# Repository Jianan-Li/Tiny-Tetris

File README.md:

# Tiny-Tetris

Click <a href="http://www.jianan.li/tiny-tetris">here</a> for more info on this project.

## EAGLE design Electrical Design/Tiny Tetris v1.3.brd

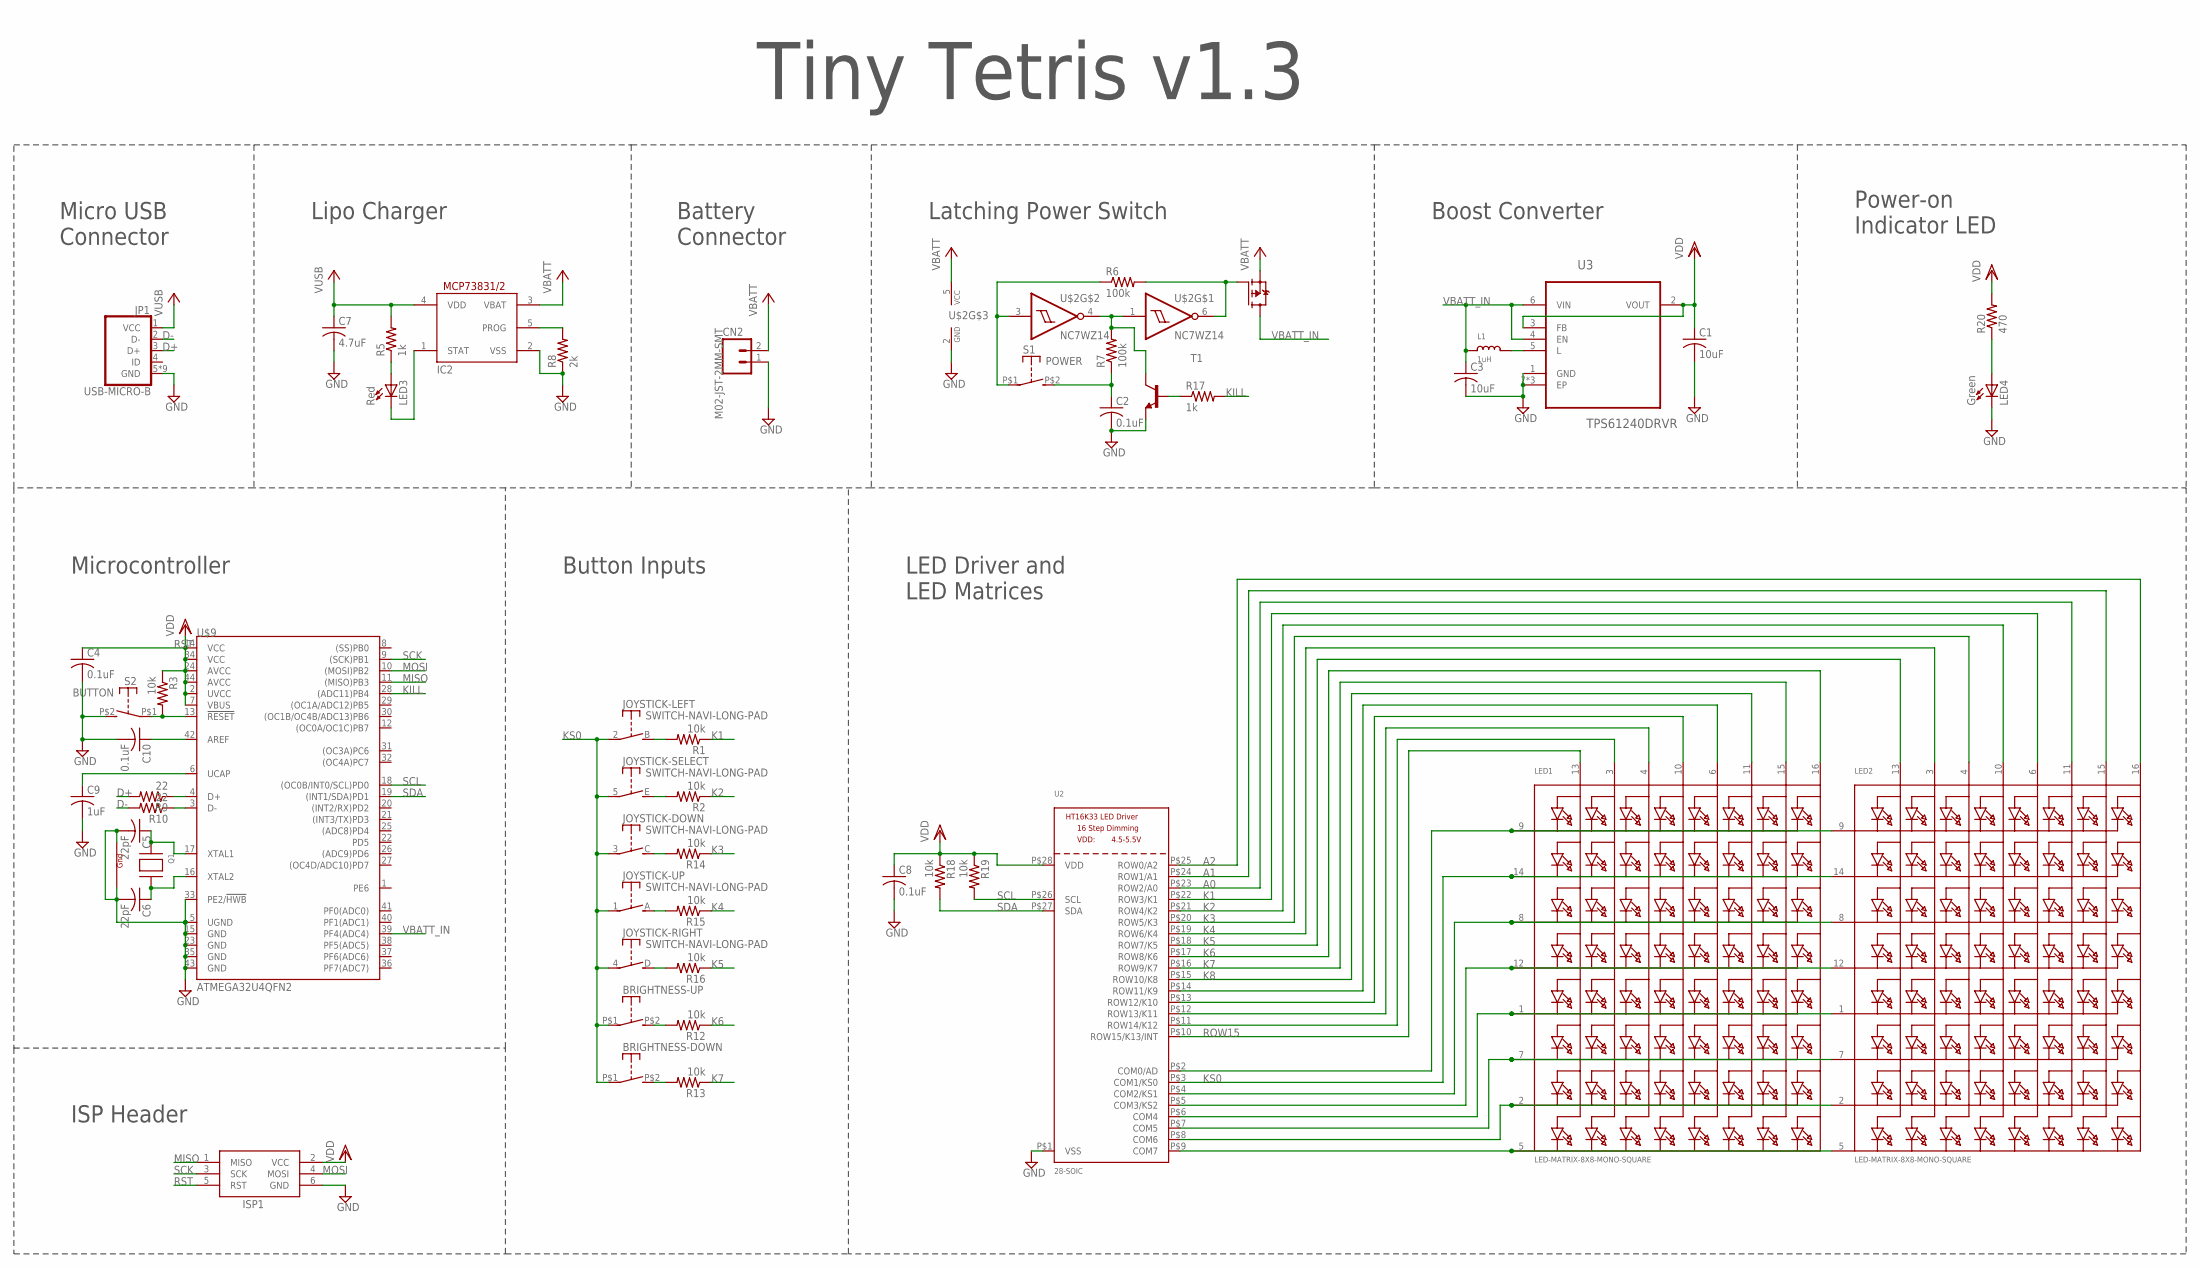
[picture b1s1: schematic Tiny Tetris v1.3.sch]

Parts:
BRIGHTNESS-DOWN: SWITCH-TACTSKRELGE010; TACT-ALPS-SKRELGE010
BRIGHTNESS-UP: SWITCH-TACTSKRELGE010; TACT-ALPS-SKRELGE010
C1, C3: 10uF; C0603K
C2, C4, C8, C10: 0.1uF; C0603K
C5, C6: 22pF; C0603K
C7: 4.7uF; C0603K
C9: 1uF; C0603K
CN2: M02-JST-2MM-SMT; 1X02_NO_SILK
IC2: MCP73831/OT; SOT23-5L
ISP1: AVRISP-6; AVRISP
JOYSTICK-: SWITCH-NAVI-LONG-PAD; JOYSTICK-NOKIA-3230-LONG-PAD
JP1: USB-MICRO-B; MICRO-USB-FCI-10103594
L1: 1uH; 0805
LED1, LED2: LED-MATRIX-8X8-MONO-SQUARE
LED3: Red; LED-0603-SIDEVIEW
LED4: Green; LED-0603-SIDEVIEW
Q1: XTAL-4-3225; NX3225
R1, R2, R3, R12, R13, R14, R15, R16, R18, R19: 10k; R0603
R5, R17: 1k; R0603
R6, R7: 100k; R0603
R8: 2k; R0603
R9, R10: 22; R0603
R20: 470; R0603
S1: POWER; TACT-ALPS-SKRELGE010
S2: BUTTON; TACT-ALPS-SKRELGE010
T1: MMBT2222ALT1-NPN-SOT23-BEC; SOT23-BEC
U2: 28-SOIC; SOP28_300MIL
U3: TPS61240DRVR; SON65P200X200X80-7N
U$1: IRLML6402; SOT23
U$2: NC7WZ14; SC-70-6
U$9: ATMEGA32U4QFN2; SPARKFUN-DIGITALIC_QFN-44-NOPAD

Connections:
A0: LED2.11 (A6), U2.P$23 (ROW2/A0)
A1: LED2.15 (A7), U2.P$24 (ROW1/A1)
A2: LED2.16 (A8), U2.P$25 (ROW0/A2)
D+: JP1.3 (D+), R9.2
D-: JP1.2 (D-), R10.2
GND: C1.2, C2.2, C3.2, C4.2, C5.2, C6.2, C7.2, C8.2, C9.2, C10.2, CN2.1, IC2.2 (VSS), ISP1.6 (GND), JP1.5 (GND), JP1.P$1 (GND), JP1.P$2 (GND), JP1.P$3 (GND), JP1.P$4 (GND), JP1.P$5 (GND), JP1.P$6 (GND), JP1.P$7 (GND), JP1.P$8 (GND), LED4.P$2 (C), Q1.2 (G2), Q1.4 (G1), R8.1, S2.P$2 (S), T1.E, U2.P$1 (VSS), U3.1 (GND), U3.7 (EP), U3.8 (EP), U3.9 (EP), U$2.2 (GND), U$9.5 (UGND), U$9.15 (GND), U$9.23 (GND), U$9.33 (PE2/!HWB), U$9.35 (GND), U$9.43 (GND)
K1: LED2.6 (A5), R1.1, U2.P$22 (ROW3/K1)
K2: LED2.10 (A4), R2.1, U2.P$21 (ROW4/K2)
K3: LED2.4 (A3), R14.1, U2.P$20 (ROW5/K3)
K4: LED2.3 (A2), R15.1, U2.P$19 (ROW6/K4)
K5: LED2.13 (A1), R16.1, U2.P$18 (ROW7/K5)
K6: LED1.16 (A8), R12.1, U2.P$17 (ROW8/K6)
K7: LED1.15 (A7), R13.1, U2.P$16 (ROW9/K7)
K8: LED1.11 (A6), U2.P$15 (ROW10/K8)
KILL: R17.2, U$9.28 ((ADC11)PB4)
KS0: BRIGHTNESS-DOWN.P$1, BRIGHTNESS-UP.P$1, JOYSTICK-.1, JOYSTICK-.2, JOYSTICK-.3, JOYSTICK-.4, JOYSTICK-.5, LED1.14 (K2), LED2.14 (K2), U2.P$3 (COM1/KS0)
MISO: ISP1.1 (MISO), U$9.11 ((MISO)PB3)
MOSI: ISP1.4 (MOSI), U$9.10 ((MOSI)PB2)
unnamed: LED1.5 (K8), LED2.5 (K8), U2.P$9 (COM7)
unnamed: LED3.P$1 (A), R5.1
unnamed: JOYSTICK-.C (S), R14.2
unnamed: R6.2, U$1.1 (G), U$2.6 (O)
unnamed: R17.1, T1.B
unnamed: R6.1, S1.P$1, U$2.3 (I)
unnamed: JOYSTICK-.E (S), R2.2
unnamed: LED1.9 (K1), LED2.9 (K1), U2.P$2 (COM0/AD)
unnamed: JOYSTICK-.D (S), R16.2
unnamed: C2.1, R7.1, S1.P$2 (S)
unnamed: JOYSTICK-.B (S), R1.2
unnamed: R7.2, T1.C, U$2.1 (I), U$2.4 (O)
unnamed: JOYSTICK-.A (S), R15.2
unnamed: C10.1, U$9.42 (AREF)
unnamed: R9.1, U$9.4 (D+)
unnamed: IC2.1 (STAT), LED3.P$2 (C)
unnamed: IC2.5 (PROG), R8.2
unnamed: R10.1, U$9.3 (D-)
unnamed: C9.1, U$9.6 (UCAP)
unnamed: BRIGHTNESS-UP.P$2 (S), R12.2
unnamed: LED1.3 (A2), U2.P$11 (ROW14/K12)
unnamed: LED1.4 (A3), U2.P$12 (ROW13/K11)
unnamed: LED1.10 (A4), U2.P$13 (ROW12/K10)
unnamed: LED1.6 (A5), U2.P$14 (ROW11/K9)
unnamed: BRIGHTNESS-DOWN.P$2 (S), R13.2
unnamed: LED4.P$1 (A), R20.1
unnamed: L1.2, U3.5 (L)
unnamed: LED1.8 (K3), LED2.8 (K3), U2.P$4 (COM2/KS1)
unnamed: C5.1, Q1.1 (X1), U$9.17 (XTAL1)
unnamed: LED1.12 (K4), LED2.12 (K4), U2.P$5 (COM3/KS2)
unnamed: LED1.1 (K5), LED2.1 (K5), U2.P$6 (COM4)
unnamed: LED1.7 (K6), LED2.7 (K6), U2.P$7 (COM5)
unnamed: LED1.2 (K7), LED2.2 (K7), U2.P$8 (COM6)
unnamed: C6.1, Q1.3 (X2), U$9.16 (XTAL2)
ROW15: LED1.13 (A1), U2.P$10 (ROW15/K13/INT)
RST: ISP1.5 (RST), R3.2, S2.P$1, U$9.13 (!RESET)
SCK: ISP1.3 (SCK), U$9.9 ((SCK)PB1)
SCL: R19.2, U2.P$26 (SCL), U$9.18 ((OC0B/INT0/SCL)PD0)
SDA: R18.2, U2.P$27 (SDA), U$9.19 ((INT1/SDA)PD1)
VBATT: CN2.2, IC2.3 (VBAT), U$1.2 (S), U$2.5 (VCC)
VBATT_IN: C3.1, L1.1, U3.4 (EN), U3.6 (VIN), U$1.3 (D), U$9.39 (PF4(ADC4))
VDD: C1.1, C4.1, C8.1, ISP1.2 (VCC), R3.1, R18.1, R19.1, R20.2, U2.P$28 (VDD), U3.2 (VOUT), U3.3 (FB), U$9.2 (UVCC), U$9.7 (VBUS), U$9.14 (VCC), U$9.24 (AVCC), U$9.34 (VCC), U$9.44 (AVCC)
VUSB: C7.1, IC2.4 (VDD), JP1.1 (VCC), R5.2

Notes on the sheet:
Tiny Tetris v1.3
Lipo Charger
LED Driver and LED Matrices
Microcontroller
Button Inputs
Boost Converter
Latching Power Switch
Micro USB Connector
Power-on Indicator LED
ISP Header
Battery Connector

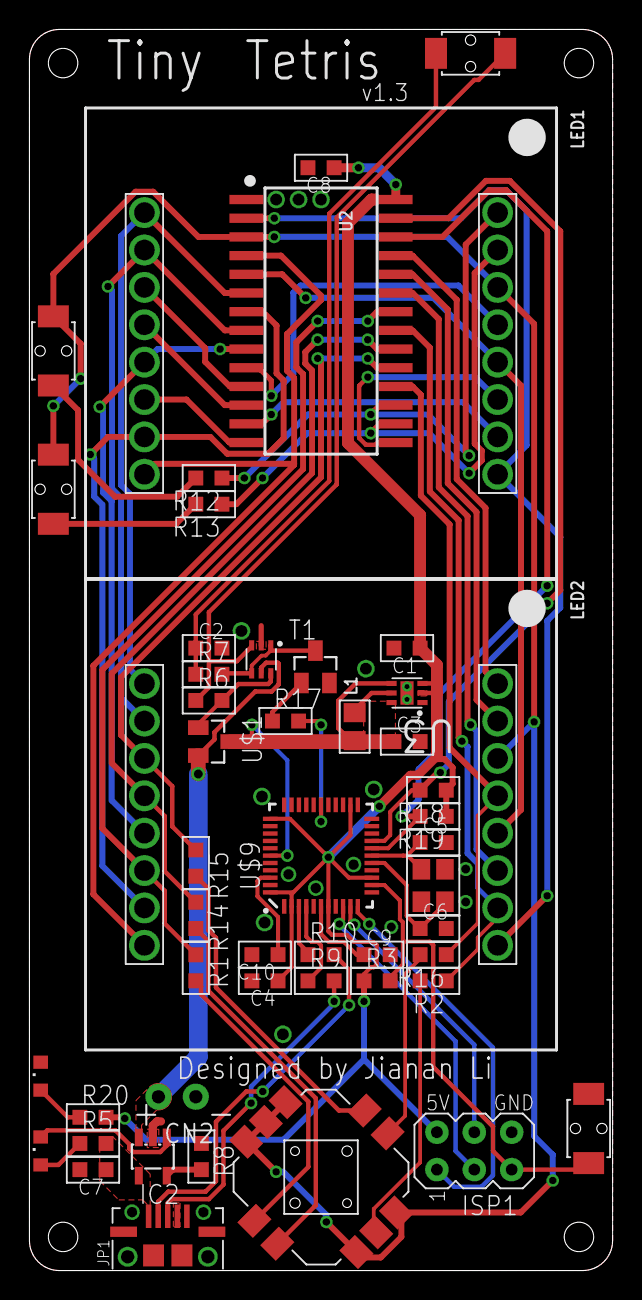
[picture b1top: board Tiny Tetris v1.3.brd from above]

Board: 2 copper layers, 39.6 x 84.3 mm, 49 parts (0 on the bottom side), 61 nets.

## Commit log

2014-08-16 add EAGLE source files
2014-08-20 add Arduino files
2014-08-20 add enclosure design
2016-12-03 Fix bug in the HT16K33 driver.
2016-12-03 Clean up the latest schematic.
2016-12-03 Change folder naming

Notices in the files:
parts and their libraries:
SparkFun-Connectors: Licensing: Creative Commons ShareAlike 4.0 International - https://creativecommons.org/licenses/by-sa/4.0
